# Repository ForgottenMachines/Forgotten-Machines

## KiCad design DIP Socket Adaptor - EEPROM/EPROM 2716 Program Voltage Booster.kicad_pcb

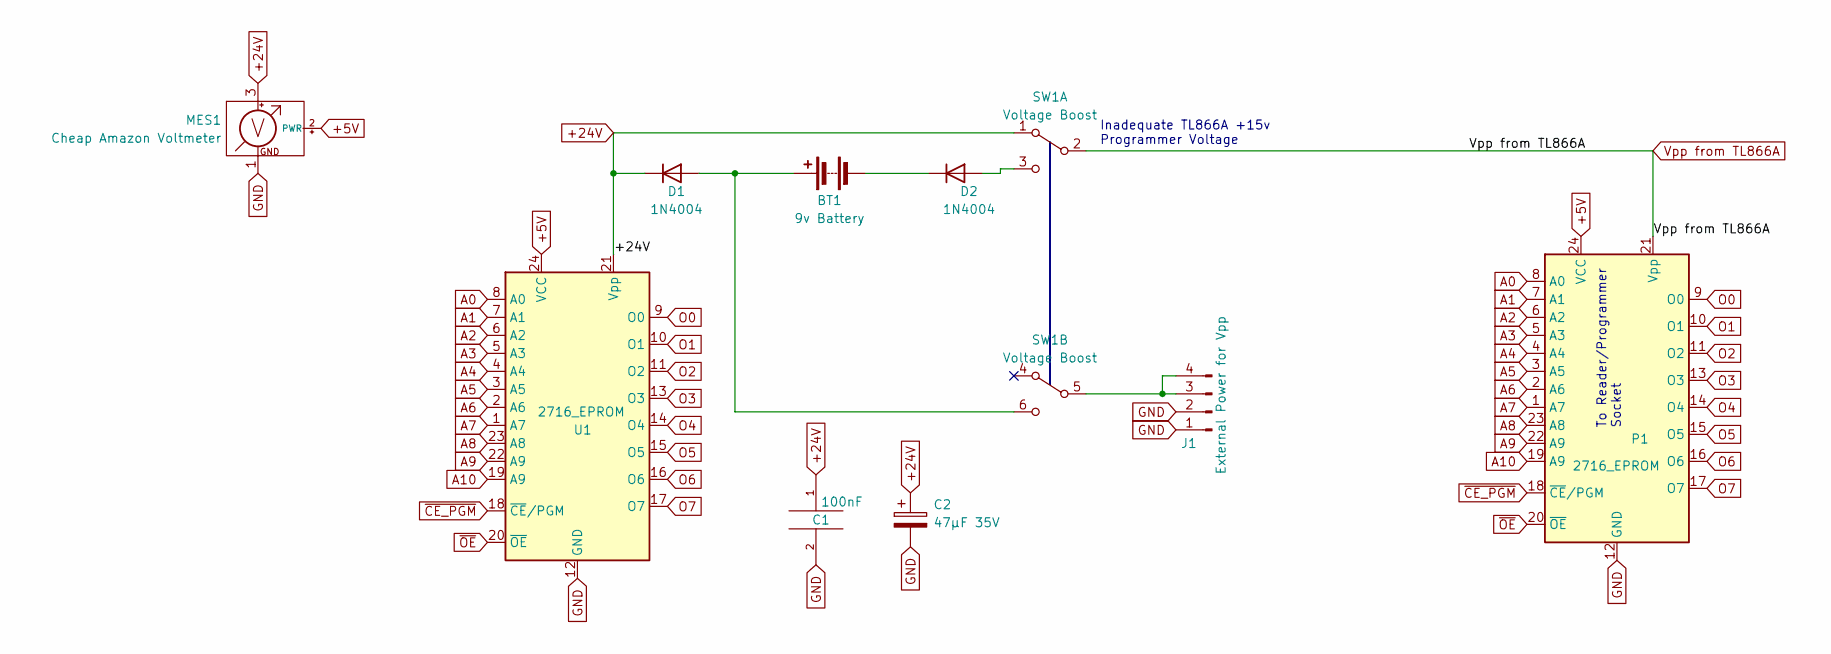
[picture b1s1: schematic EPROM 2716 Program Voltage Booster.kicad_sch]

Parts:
BT1: 9v Battery; 9v Battery PCB-Mount
C1: 100nF; Disc Capacitor Common Entrex Trapezoid
C2: 47μF 35V; CP_Radial_D5.0mm_P2.50mm
D1, D2: 1N4004; D_DO-41_SOD81_P10.16mm_Horizontal
J1: External Power for Vpp; PinHeader_1x04_P2.54mm_Vertical
MES1: Cheap Amazon Voltmeter
P1: 2716_EPROM; DIP-24_W15.24mm
SW1: Voltage Boost; SW_Slide_DPDT
U1: 2716_EPROM; DIP-24_W15.24mm

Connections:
+5V: MES1.2 (PWR), P1.24 (VCC), U1.24 (VCC)
+24V: C1.1, C2.1, D1.1 (K), MES1.3, SW1.1 (A), U1.21 (Vpp)
A0: P1.8 (A0), U1.8 (A0)
A1: P1.7 (A1), U1.7 (A1)
A2: P1.6 (A2), U1.6 (A2)
A3: P1.5 (A3), U1.5 (A3)
A4: P1.4 (A4), U1.4 (A4)
A5: P1.3 (A5), U1.3 (A5)
A6: P1.2 (A6), U1.2 (A6)
A7: P1.1 (A7), U1.1 (A7)
A8: P1.23 (A8), U1.23 (A8)
A9: P1.22 (A9), U1.22 (A9)
A10: P1.19 (A9), U1.19 (A9)
GND: C1.2, C2.2, J1.1, J1.2, MES1.1, MES1.4, MES1.5, P1.12 (GND), U1.12 (GND)
unnamed: BT1.1 (+), D1.2 (A), SW1.6 (C)
unnamed: BT1.2 (-), D2.1 (K)
unnamed: D2.2 (A), SW1.3 (C)
unnamed: J1.3, J1.4, SW1.5 (B)
O0: P1.9 (O0), U1.9 (O0)
O1: P1.10 (O1), U1.10 (O1)
O2: P1.11 (O2), U1.11 (O2)
O3: P1.13 (O3), U1.13 (O3)
O4: P1.14 (O4), U1.14 (O4)
O5: P1.15 (O5), U1.15 (O5)
O6: P1.16 (O6), U1.16 (O6)
O7: P1.17 (O7), U1.17 (O7)
Vpp from TL866A: P1.21 (Vpp), SW1.2 (B)
~CE_PGM: P1.18 (~CE/PGM), U1.18 (~CE/PGM)
~OE: P1.20 (~OE), U1.20 (~OE)

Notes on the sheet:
To Reader/Programmer Socket
Inadequate TL866A +15v Programmer Voltage

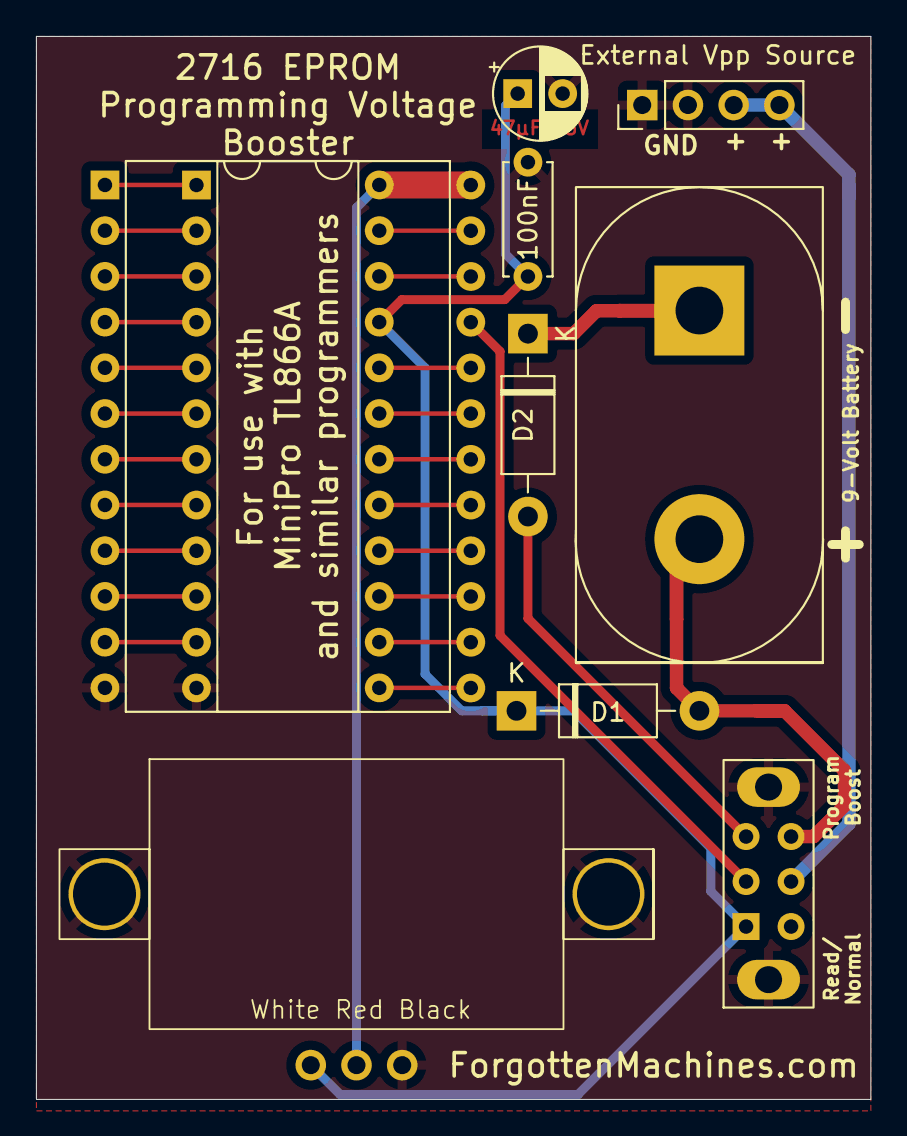
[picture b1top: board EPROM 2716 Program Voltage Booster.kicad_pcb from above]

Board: 2 copper layers, 46.4 x 59.1 mm, 10 parts (0 on the bottom side), 29 nets.

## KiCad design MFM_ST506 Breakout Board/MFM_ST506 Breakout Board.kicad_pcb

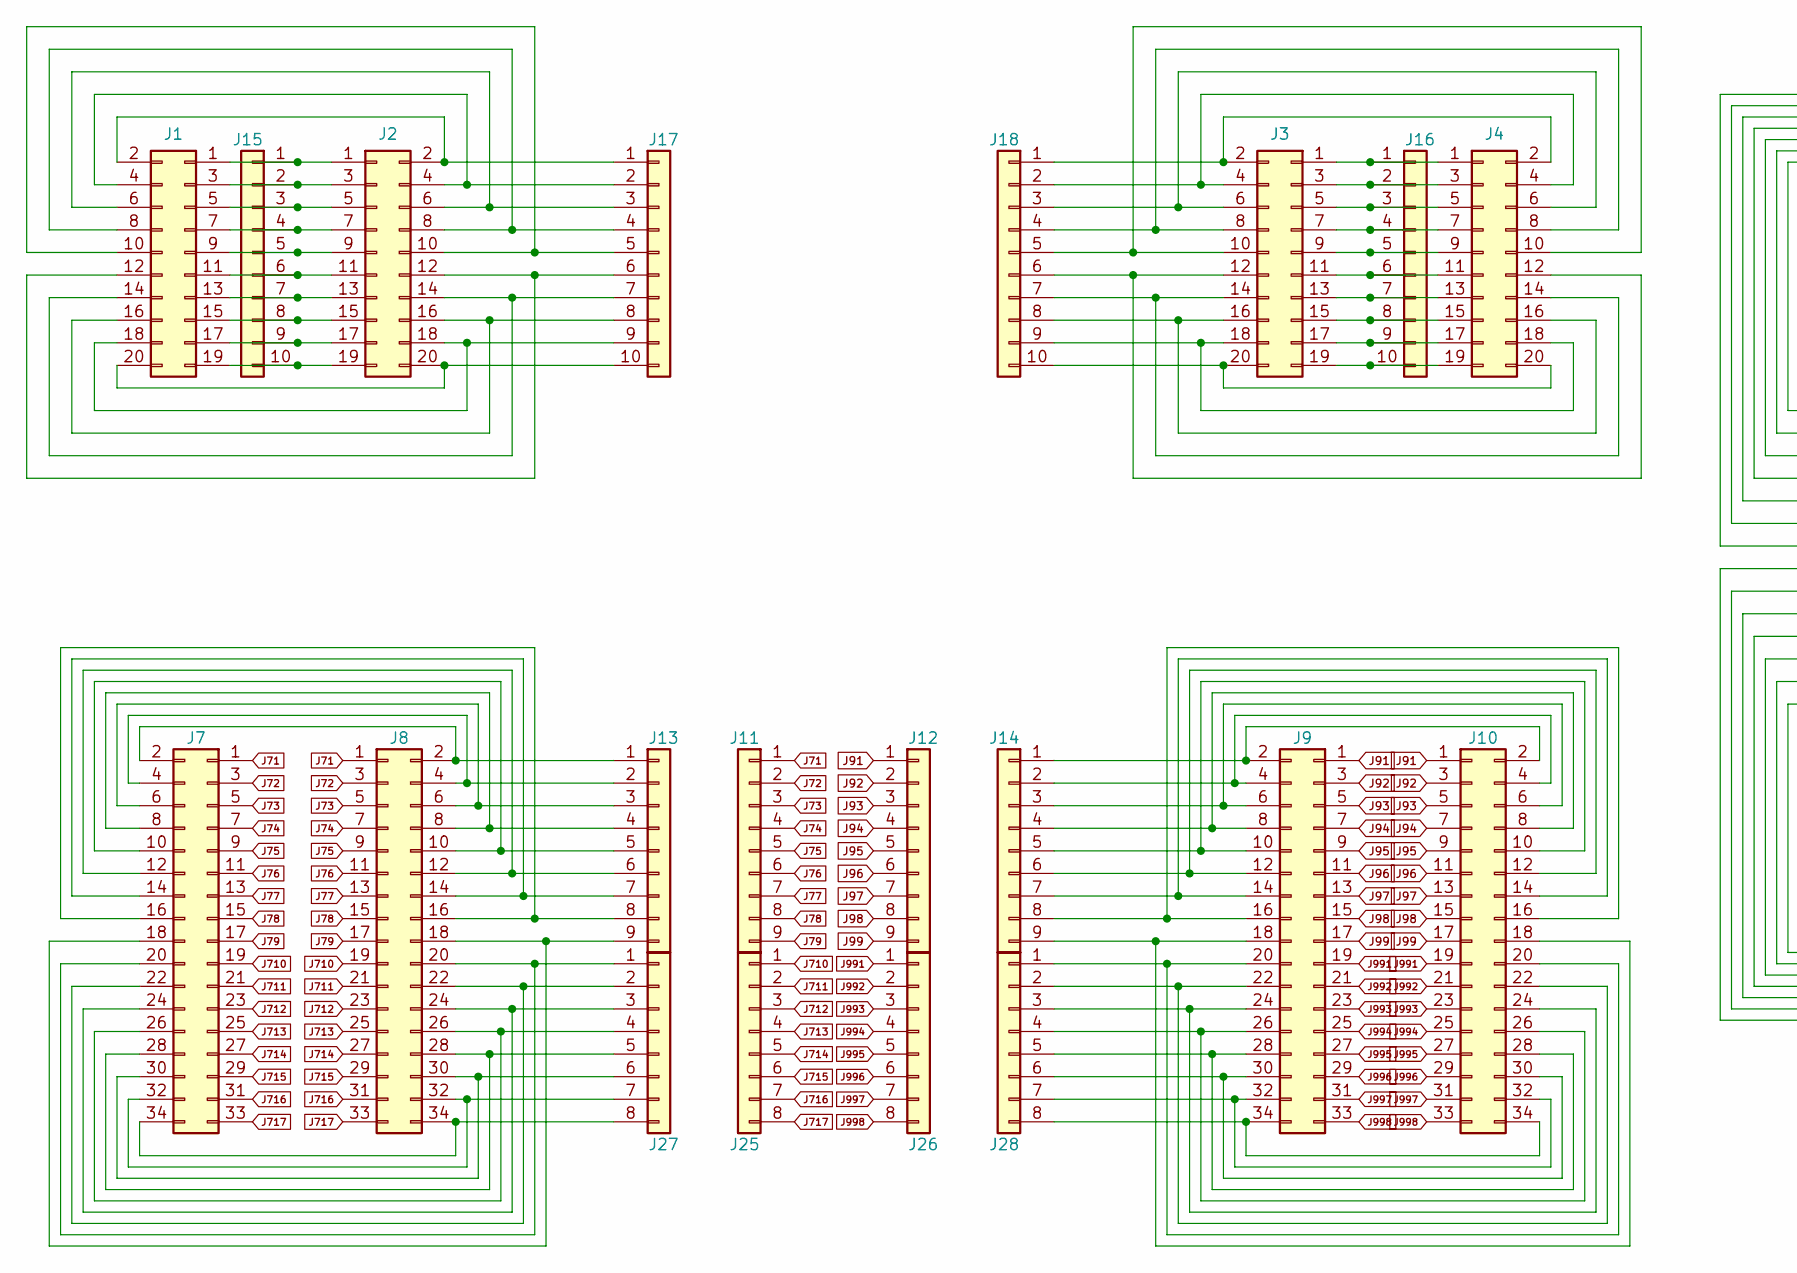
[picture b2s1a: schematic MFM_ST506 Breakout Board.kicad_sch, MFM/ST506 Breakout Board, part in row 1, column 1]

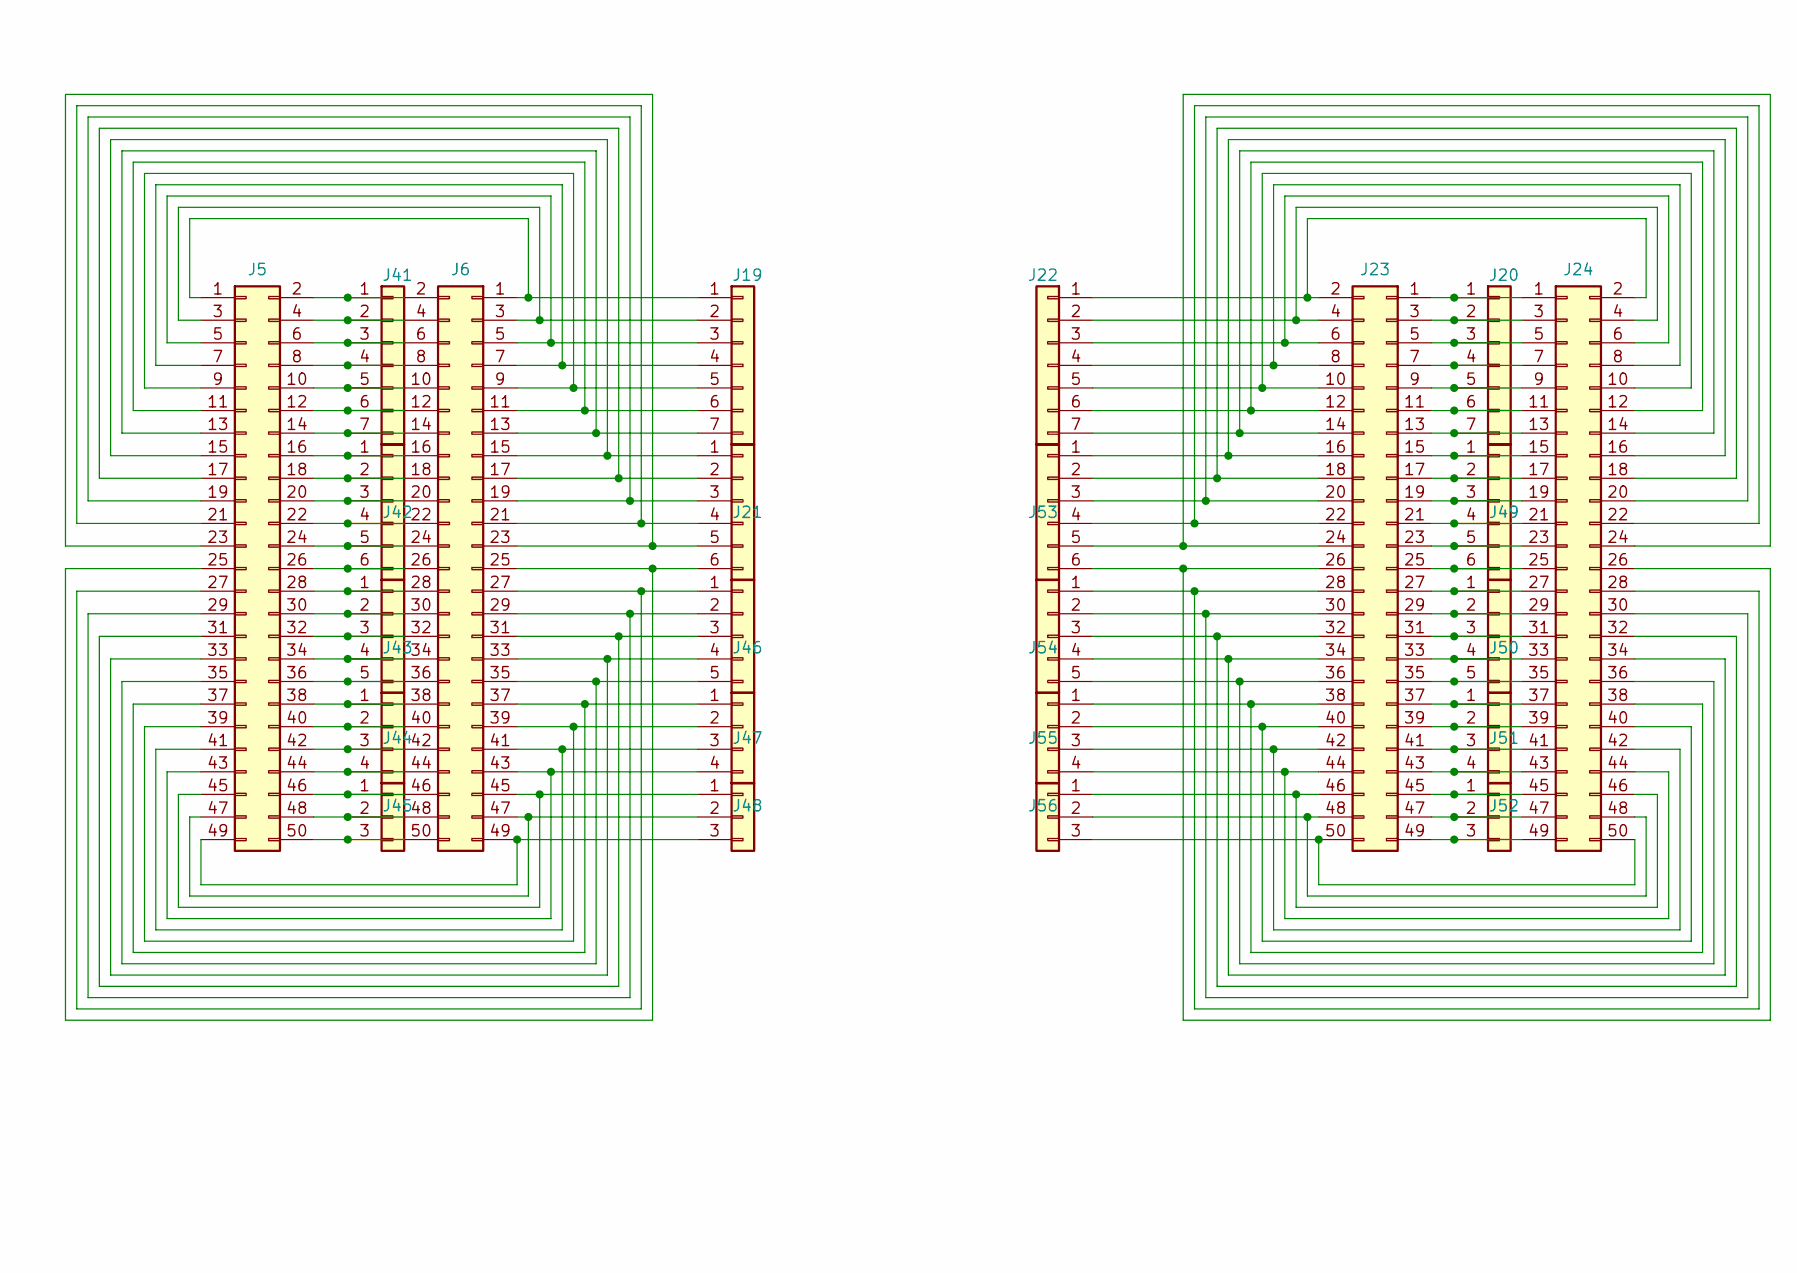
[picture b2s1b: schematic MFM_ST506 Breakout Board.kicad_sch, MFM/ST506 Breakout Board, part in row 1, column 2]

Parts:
J1, J2, J3, J4: Conn_02x10_Odd_Even; PinHeader_2x10_P2.54mm_Vertical
J5, J6, J23, J24: Conn_02x25_Odd_Even; PinHeader_2x25_P2.54mm_Vertical
J7, J8, J9, J10: Conn_02x17_Odd_Even; PinHeader_2x17_P2.54mm_Vertical
J11, J12, J13, J14: Conn_01x09; PinHeader_1x09_P2.54mm_Vertical
J15, J16, J17, J18: Conn_01x10; PinSocket_1x10_P2.54mm_Vertical
J19, J20, J22, J41: Conn_01x07; PinHeader_1x07_P2.54mm_Vertical
J21, J42, J49, J53: Conn_01x06; PinHeader_1x06_P2.54mm_Vertical
J25, J26, J27, J28: Conn_01x08; PinHeader_1x08_P2.54mm_Vertical
J43, J46, J50, J54: Conn_01x05; PinHeader_1x05_P2.54mm_Vertical
J44, J47, J51, J55: Conn_01x04; PinHeader_1x04_P2.54mm_Vertical
J45, J48, J52, J56: Conn_01x03; PinHeader_1x03_P2.54mm_Vertical

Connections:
J71: J7.1, J8.1, J11.1
J72: J7.3, J8.3, J11.2
J73: J7.5, J8.5, J11.3
J74: J7.7, J8.7, J11.4
J75: J7.9, J8.9, J11.5
J76: J7.11, J8.11, J11.6
J77: J7.13, J8.13, J11.7
J78: J7.15, J8.15, J11.8
J79: J7.17, J8.17, J11.9
J91: J9.1, J10.1, J12.1
J92: J9.3, J10.3, J12.2
J93: J9.5, J10.5, J12.3
J94: J9.7, J10.7, J12.4
J95: J9.9, J10.9, J12.5
J96: J9.11, J10.11, J12.6
J97: J9.13, J10.13, J12.7
J98: J9.15, J10.15, J12.8
J99: J9.17, J10.17, J12.9
J710: J7.19, J8.19, J25.1
J711: J7.21, J8.21, J25.2
J712: J7.23, J8.23, J25.3
J713: J7.25, J8.25, J25.4
J714: J7.27, J8.27, J25.5
J715: J7.29, J8.29, J25.6
J716: J7.31, J8.31, J25.7
J717: J7.33, J8.33, J25.8
J991: J9.19, J10.19, J26.1
J992: J9.21, J10.21, J26.2
J993: J9.23, J10.23, J26.3
J994: J9.25, J10.25, J26.4
J995: J9.27, J10.27, J26.5
J996: J9.29, J10.29, J26.6
J997: J9.31, J10.31, J26.7
J998: J9.33, J10.33, J26.8
unnamed: J1.1, J2.1, J15.1
unnamed: J1.2, J2.2, J17.1
unnamed: J1.3, J2.3, J15.2
unnamed: J1.4, J2.4, J17.2
unnamed: J1.5, J2.5, J15.3
unnamed: J1.6, J2.6, J17.3
unnamed: J1.7, J2.7, J15.4
unnamed: J1.8, J2.8, J17.4
unnamed: J1.9, J2.9, J15.5
unnamed: J1.10, J2.10, J17.5
unnamed: J1.11, J2.11, J15.6
unnamed: J1.12, J2.12, J17.6
unnamed: J1.13, J2.13, J15.7
unnamed: J1.14, J2.14, J17.7
unnamed: J1.15, J2.15, J15.8
unnamed: J1.16, J2.16, J17.8
unnamed: J1.17, J2.17, J15.9
unnamed: J1.18, J2.18, J17.9
unnamed: J1.19, J2.19, J15.10
unnamed: J1.20, J2.20, J17.10
unnamed: J9.2, J10.2, J14.1
unnamed: J9.4, J10.4, J14.2
unnamed: J9.6, J10.6, J14.3
unnamed: J9.8, J10.8, J14.4
unnamed: J9.10, J10.10, J14.5
unnamed: J9.12, J10.12, J14.6
unnamed: J9.14, J10.14, J14.7
unnamed: J9.16, J10.16, J14.8
unnamed: J9.18, J10.18, J14.9
unnamed: J9.20, J10.20, J28.1
unnamed: J9.22, J10.22, J28.2
unnamed: J9.24, J10.24, J28.3
unnamed: J9.26, J10.26, J28.4
unnamed: J9.28, J10.28, J28.5
unnamed: J9.30, J10.30, J28.6
unnamed: J9.32, J10.32, J28.7
unnamed: J9.34, J10.34, J28.8
unnamed: J7.2, J8.2, J13.1
unnamed: J7.4, J8.4, J13.2
unnamed: J7.6, J8.6, J13.3
unnamed: J7.8, J8.8, J13.4
unnamed: J7.10, J8.10, J13.5
unnamed: J7.12, J8.12, J13.6
unnamed: J7.14, J8.14, J13.7
unnamed: J7.16, J8.16, J13.8
unnamed: J7.18, J8.18, J13.9
unnamed: J3.1, J4.1, J16.1
unnamed: J3.3, J4.3, J16.2
unnamed: J3.5, J4.5, J16.3
unnamed: J3.7, J4.7, J16.4
unnamed: J3.9, J4.9, J16.5
unnamed: J3.11, J4.11, J16.6
unnamed: J3.13, J4.13, J16.7
unnamed: J3.15, J4.15, J16.8
unnamed: J3.17, J4.17, J16.9
unnamed: J3.19, J4.19, J16.10
unnamed: J3.2, J4.2, J18.1
unnamed: J3.4, J4.4, J18.2
unnamed: J3.6, J4.6, J18.3
unnamed: J3.8, J4.8, J18.4
unnamed: J3.10, J4.10, J18.5
unnamed: J3.12, J4.12, J18.6
unnamed: J3.14, J4.14, J18.7
unnamed: J3.16, J4.16, J18.8
unnamed: J3.18, J4.18, J18.9
unnamed: J3.20, J4.20, J18.10
unnamed: J5.1, J6.1, J19.1
unnamed: J5.3, J6.3, J19.2
unnamed: J5.5, J6.5, J19.3
unnamed: J5.7, J6.7, J19.4
unnamed: J5.9, J6.9, J19.5
unnamed: J5.11, J6.11, J19.6
unnamed: J5.13, J6.13, J19.7
unnamed: J20.1, J23.1, J24.1
unnamed: J20.2, J23.3, J24.3
unnamed: J20.3, J23.5, J24.5
unnamed: J20.4, J23.7, J24.7
unnamed: J20.5, J23.9, J24.9
unnamed: J20.6, J23.11, J24.11
unnamed: J20.7, J23.13, J24.13
unnamed: J5.15, J6.15, J21.1
unnamed: J5.17, J6.17, J21.2
unnamed: J5.19, J6.19, J21.3
unnamed: J5.21, J6.21, J21.4
unnamed: J5.23, J6.23, J21.5
unnamed: J5.25, J6.25, J21.6
unnamed: J22.1, J23.2, J24.2
unnamed: J22.2, J23.4, J24.4
unnamed: J22.3, J23.6, J24.6
unnamed: J22.4, J23.8, J24.8
unnamed: J22.5, J23.10, J24.10
unnamed: J22.6, J23.12, J24.12
unnamed: J22.7, J23.14, J24.14
unnamed: J23.15, J24.15, J49.1
unnamed: J23.16, J24.16, J53.1
unnamed: J23.17, J24.17, J49.2
unnamed: J23.18, J24.18, J53.2
unnamed: J23.19, J24.19, J49.3
unnamed: J23.20, J24.20, J53.3
unnamed: J23.21, J24.21, J49.4
unnamed: J23.22, J24.22, J53.4
unnamed: J23.23, J24.23, J49.5
unnamed: J23.24, J24.24, J53.5
unnamed: J23.25, J24.25, J49.6
unnamed: J23.26, J24.26, J53.6
unnamed: J23.27, J24.27, J50.1
unnamed: J23.28, J24.28, J54.1
unnamed: J23.29, J24.29, J50.2
unnamed: J23.30, J24.30, J54.2
unnamed: J23.31, J24.31, J50.3
unnamed: J23.32, J24.32, J54.3
unnamed: J23.33, J24.33, J50.4
unnamed: J23.34, J24.34, J54.4
unnamed: J23.35, J24.35, J50.5
unnamed: J23.36, J24.36, J54.5
unnamed: J23.37, J24.37, J51.1
unnamed: J23.38, J24.38, J55.1
unnamed: J23.39, J24.39, J51.2
unnamed: J23.40, J24.40, J55.2
unnamed: J23.41, J24.41, J51.3
unnamed: J23.42, J24.42, J55.3
unnamed: J23.43, J24.43, J51.4
unnamed: J23.44, J24.44, J55.4
unnamed: J23.45, J24.45, J52.1
unnamed: J23.46, J24.46, J56.1
unnamed: J23.47, J24.47, J52.2
unnamed: J23.48, J24.48, J56.2
unnamed: J23.49, J24.49, J52.3
unnamed: J23.50, J24.50, J56.3
unnamed: J7.20, J8.20, J27.1
unnamed: J7.22, J8.22, J27.2
unnamed: J7.24, J8.24, J27.3
unnamed: J7.26, J8.26, J27.4
unnamed: J7.28, J8.28, J27.5
unnamed: J7.30, J8.30, J27.6
unnamed: J7.32, J8.32, J27.7
unnamed: J7.34, J8.34, J27.8
unnamed: J5.2, J6.2, J41.1
unnamed: J5.4, J6.4, J41.2
unnamed: J5.6, J6.6, J41.3
unnamed: J5.8, J6.8, J41.4
unnamed: J5.10, J6.10, J41.5
unnamed: J5.12, J6.12, J41.6
unnamed: J5.14, J6.14, J41.7
unnamed: J5.16, J6.16, J42.1
unnamed: J5.18, J6.18, J42.2
unnamed: J5.20, J6.20, J42.3
unnamed: J5.22, J6.22, J42.4
unnamed: J5.24, J6.24, J42.5
unnamed: J5.26, J6.26, J42.6
unnamed: J5.28, J6.28, J43.1
unnamed: J5.30, J6.30, J43.2
unnamed: J5.32, J6.32, J43.3
unnamed: J5.34, J6.34, J43.4
unnamed: J5.36, J6.36, J43.5
unnamed: J5.38, J6.38, J44.1
unnamed: J5.40, J6.40, J44.2
unnamed: J5.42, J6.42, J44.3
unnamed: J5.44, J6.44, J44.4
unnamed: J5.46, J6.46, J45.1
unnamed: J5.48, J6.48, J45.2
unnamed: J5.50, J6.50, J45.3
unnamed: J5.27, J6.27, J46.1
unnamed: J5.29, J6.29, J46.2
unnamed: J5.31, J6.31, J46.3
unnamed: J5.33, J6.33, J46.4
unnamed: J5.35, J6.35, J46.5
unnamed: J5.37, J6.37, J47.1
unnamed: J5.39, J6.39, J47.2
unnamed: J5.41, J6.41, J47.3
unnamed: J5.43, J6.43, J47.4
unnamed: J5.45, J6.45, J48.1
unnamed: J5.47, J6.47, J48.2
unnamed: J5.49, J6.49, J48.3

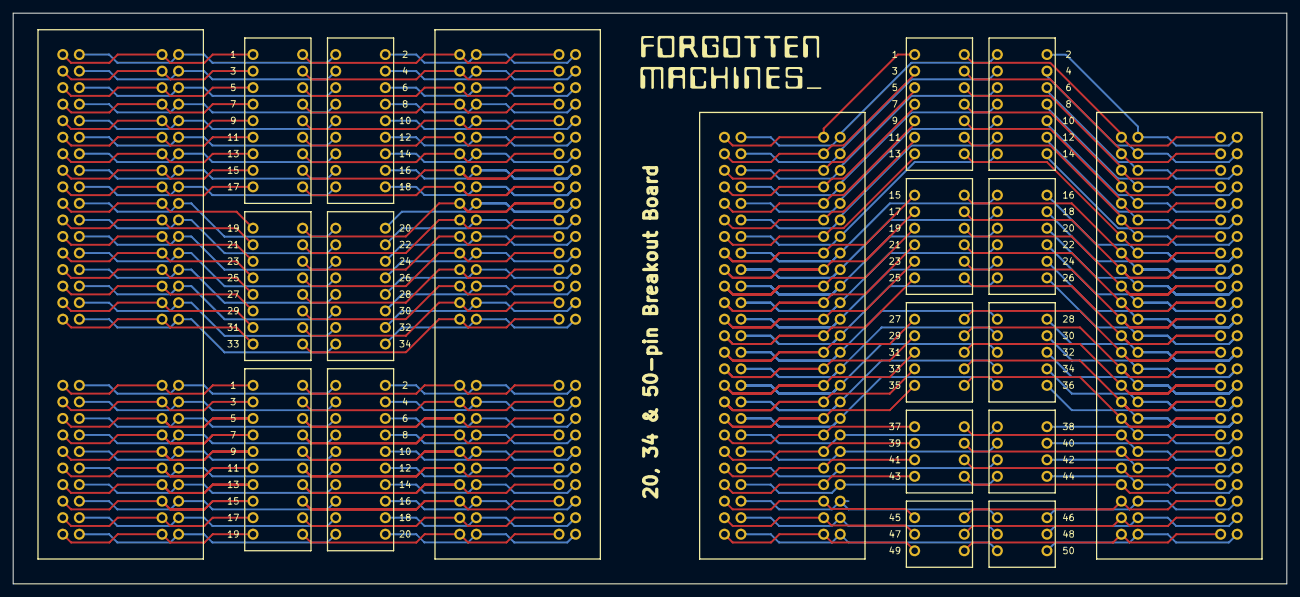
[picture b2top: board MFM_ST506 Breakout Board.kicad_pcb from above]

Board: 2 copper layers, 195.6 x 87.6 mm, 44 parts (0 on the bottom side), 208 nets.

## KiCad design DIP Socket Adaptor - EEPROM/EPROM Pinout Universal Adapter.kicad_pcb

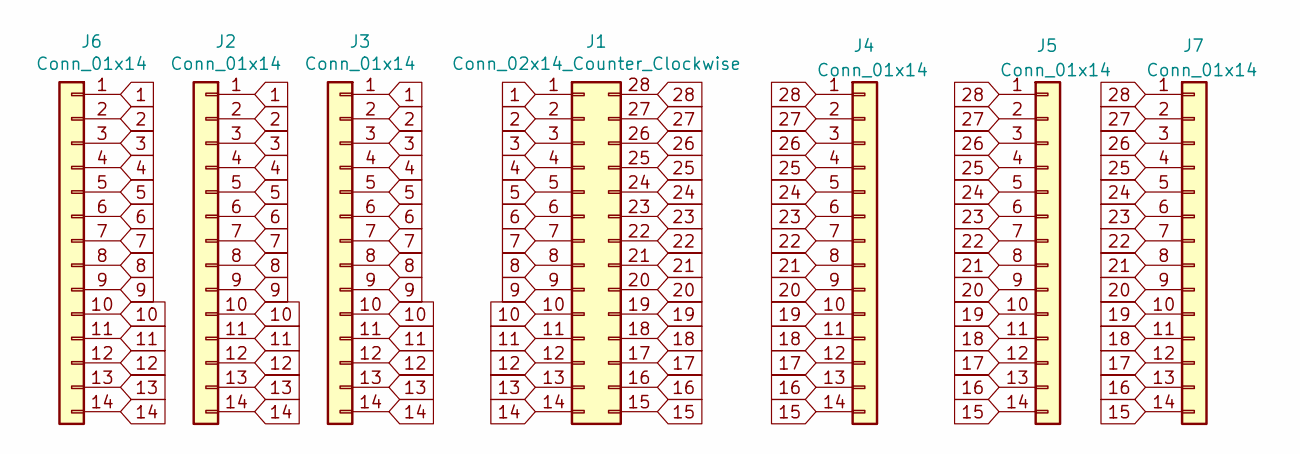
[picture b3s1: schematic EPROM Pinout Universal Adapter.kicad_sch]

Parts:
J1: Conn_02x14_Counter_Clockwise; DIP-28_W15.24mm
J2, J3, J6, J7: Conn_01x14; PinHeader_1x14_P2.54mm_Vertical
J4, J5: Conn_01x14; PinHeader_1x14_P2.54mm_Vertical2

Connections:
1: J1.1, J2.1, J3.1, J6.1
2: J1.2, J2.2, J3.2, J6.2
3: J1.3, J2.3, J3.3, J6.3
4: J1.4, J2.4, J3.4, J6.4
5: J1.5, J2.5, J3.5, J6.5
6: J1.6, J2.6, J3.6, J6.6
7: J1.7, J2.7, J3.7, J6.7
8: J1.8, J2.8, J3.8, J6.8
9: J1.9, J2.9, J3.9, J6.9
10: J1.10, J2.10, J3.10, J6.10
11: J1.11, J2.11, J3.11, J6.11
12: J1.12, J2.12, J3.12, J6.12
13: J1.13, J2.13, J3.13, J6.13
14: J1.14, J2.14, J3.14, J6.14
15: J1.15, J4.14, J5.14, J7.14
16: J1.16, J4.13, J5.13, J7.13
17: J1.17, J4.12, J5.12, J7.12
18: J1.18, J4.11, J5.11, J7.11
19: J1.19, J4.10, J5.10, J7.10
20: J1.20, J4.9, J5.9, J7.9
21: J1.21, J4.8, J5.8, J7.8
22: J1.22, J4.7, J5.7, J7.7
23: J1.23, J4.6, J5.6, J7.6
24: J1.24, J4.5, J5.5, J7.5
25: J1.25, J4.4, J5.4, J7.4
26: J1.26, J4.3, J5.3, J7.3
27: J1.27, J4.2, J5.2, J7.2
28: J1.28, J4.1, J5.1, J7.1

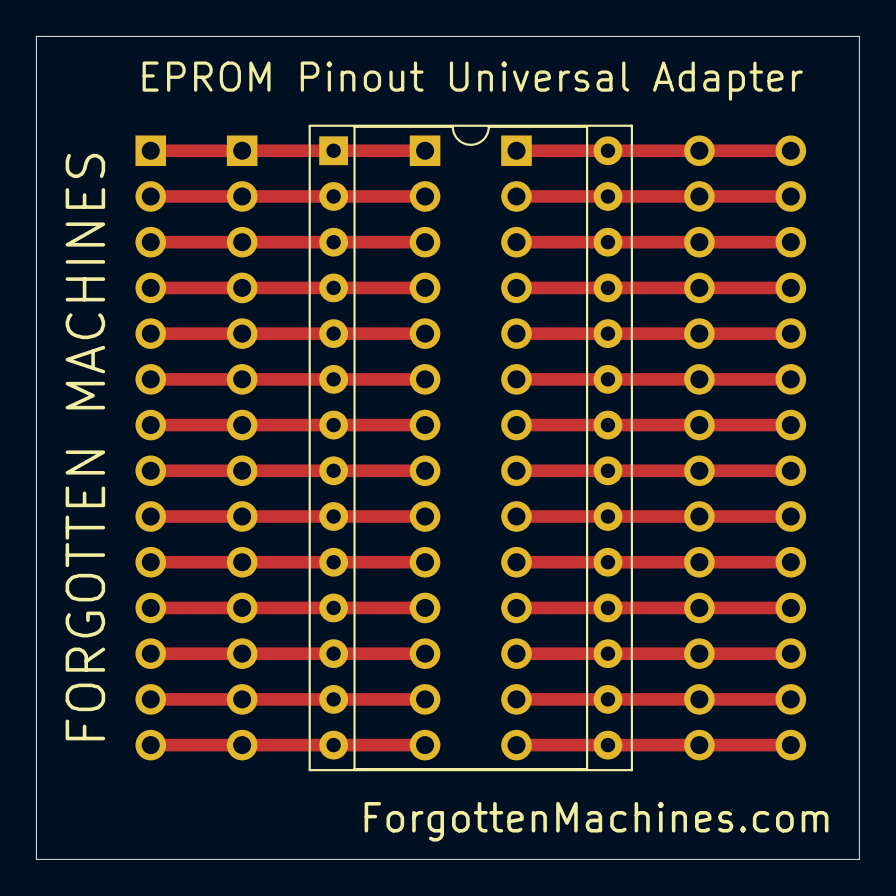
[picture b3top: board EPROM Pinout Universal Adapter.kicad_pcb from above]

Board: 2 copper layers, 45.7 x 45.7 mm, 7 parts (0 on the bottom side), 28 nets.

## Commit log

2024-01-15 logo!
2024-01-26 image
2024-01-30 KiCad
2024-02-02 syjm
2024-02-03 DG User's Group 1
2024-02-04 FM Logo
2024-02-04 unknown
2024-02-05 experiments
2024-02-05 Logos
2024-02-06 footprints
2024-02-06 Add Footprints
2024-02-06 updated footprints
2024-02-07 Whoops
2024-02-09 LED Bars 3D
2024-02-10 Nova Board Jumper Footprints
2024-02-12 Logo
2024-02-17 3.96mm headers
2024-03-16 EPROM adapter & ST506 Adapter
2024-03-16 Add boards
2024-03-25 Signetics 8281
2024-03-25 82S129/6
2024-03-27 EEPROM boards
2024-03-27 2716 Vpp boost
2024-03-27 2716 Adapter
2024-03-27 build
2024-04-02 lots-o-stuff
2024-04-20 S100 Socket Update
2024-04-21 atx psu
2025-03-19 Patreon
2025-03-19 First patreon
